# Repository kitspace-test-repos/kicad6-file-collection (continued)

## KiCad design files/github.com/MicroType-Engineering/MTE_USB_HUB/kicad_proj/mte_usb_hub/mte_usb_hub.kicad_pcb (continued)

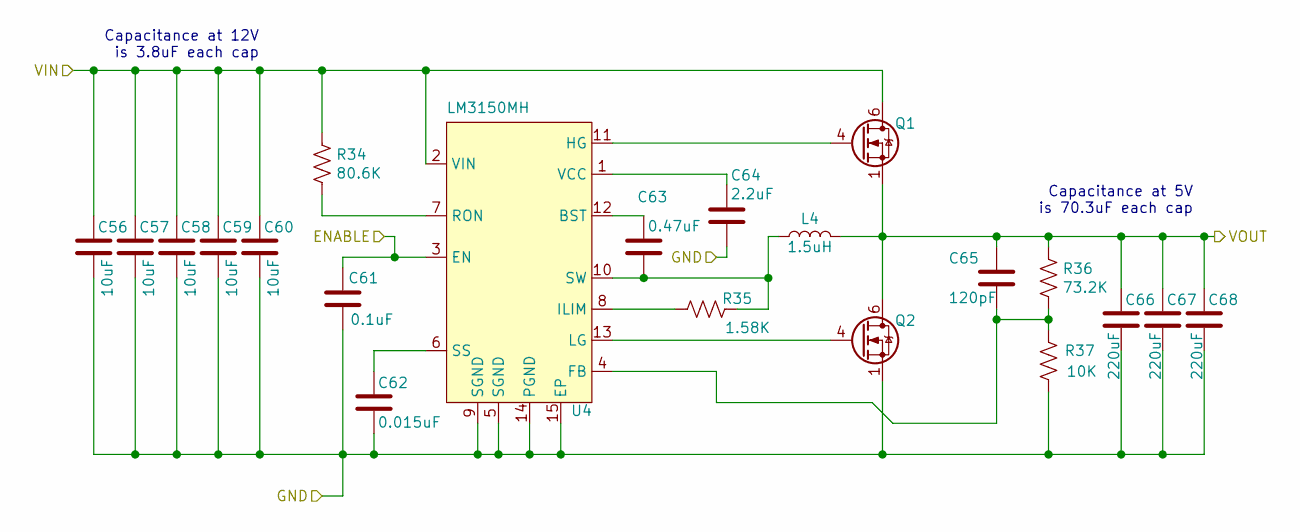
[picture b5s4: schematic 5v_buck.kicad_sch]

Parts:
C56, C57, C58, C59, C60: GRM31CR71E106KA12L; CAPACITOR_1206N
C61: CC0402KRX5R7BB104; CAPACITOR_0402N
C62: TMK105BJ153KV-F; CAPACITOR_0402N
C63: TMK105ABJ474KV-F; CAPACITOR_0402N
C64: TMK105CBJ225MV-F; CAPACITOR_0402N
C65: C0402C121J3GAC7867; CAPACITOR_0402N
C66, C67, C68: GRM32ER60J227ME05L; CAPACITOR_1210N
L4: SRP1270-1R5M; INDM1350X1350X700L250X300N
Q1: CSD16342Q5A
Q2: CSD17577Q5AT; CSD16342Q5A
R34: RC0402FR-0780K6L; RESISTOR_0402N
R35: RC0402FR-071K58L; RESISTOR_0402N
R36: RC0402FR-0773K2L; RESISTOR_0402N
R37: RC0402JR-0710KL; RESISTOR_0402N
U4: LM3150MH; SOP15P65_500X640X110L60X24T310X300N

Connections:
+5V: C65.1, C66.1, C67.1, C68.1, L4.2, Q1.1 (S), Q1.2 (S), Q1.3 (S), Q2.5 (D), Q2.6 (D), Q2.7 (D), Q2.8 (D), R36.1; also elsewhere on the board
+12V: C56.1, C57.1, C58.1, C59.1, C60.1, Q1.5 (D), Q1.6 (D), Q1.7 (D), Q1.8 (D), R34.1, U4.2 (VIN); also elsewhere on the board
/5V Buck/ENABLE: C61.2, U4.3 (EN)
GND: C56.2, C57.2, C58.2, C59.2, C60.2, C61.1, C62.2, C64.2, C66.2, C67.2, C68.2, Q2.1 (S), Q2.2 (S), Q2.3 (S), R37.2, U4.5 (SGND), U4.9 (SGND), U4.14 (PGND), U4.15 (EP); also elsewhere on the board
unnamed: C62.1, U4.6 (SS)
unnamed: C63.1, U4.12 (BST)
unnamed: C63.2, L4.1, R35.2, U4.10 (SW)
unnamed: C64.1, U4.1 (VCC)
unnamed: C65.2, R36.2, R37.1, U4.4 (FB)
unnamed: Q1.4 (G), U4.11 (HG)
unnamed: Q2.4 (G), U4.13 (LG)
unnamed: R34.2, U4.7 (RON)
unnamed: R35.1, U4.8 (ILIM)

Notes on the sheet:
Capacitance at 12V is 3.8uF each cap
Capacitance at 5V is 70.3uF each cap

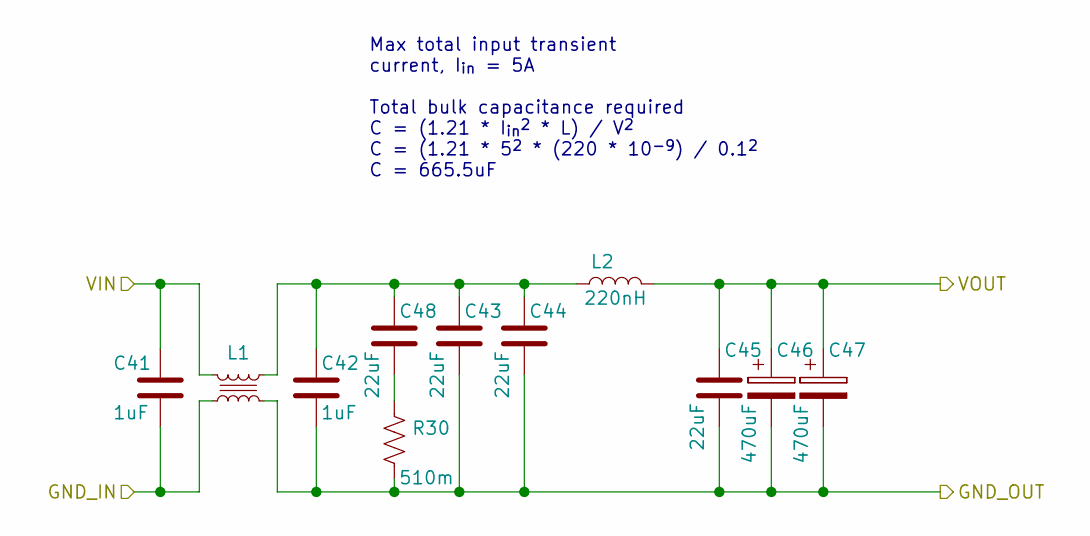
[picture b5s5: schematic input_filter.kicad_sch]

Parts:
C41, C42: CC0603KRX5R9BB105; CAPACITOR_0603N
C43, C44, C45, C48: GCJ32EC71E226KE02; CAPACITOR_1210N
C46, C47: EEE-HAE471UAP; CAPAE1030X1080L350X120N
L1: ACM1211-701-2PL-TL01
L2: FCUL0624-H-R22M=P3; INDM730X660X240L150X140N
R30: RL1206JR-070R51L; RESISTOR_1206N

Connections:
+12V: C45.1, C46.1, C47.1, L2.2; also elsewhere on the board
/INPUT FILTER/GND_IN: C41.2, L1.2; also elsewhere on the board
/INPUT FILTER/VIN: C41.1, L1.1; also elsewhere on the board
GND: C42.2, C43.2, C44.2, C45.2, C46.2, C47.2, L1.3, R30.2; also elsewhere on the board
unnamed: C42.1, C43.1, C44.1, C48.1, L1.4, L2.1
unnamed: C48.2, R30.1

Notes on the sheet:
Max total input transient current, I_{in} = 5A Total bulk capacitance required C = (1.21 * I_{in}^{2} * L) / V^{2} C = (1.21 * 5^{2} * (220 * 10^{-9}) / 0.1^{2} C = 665.5uF

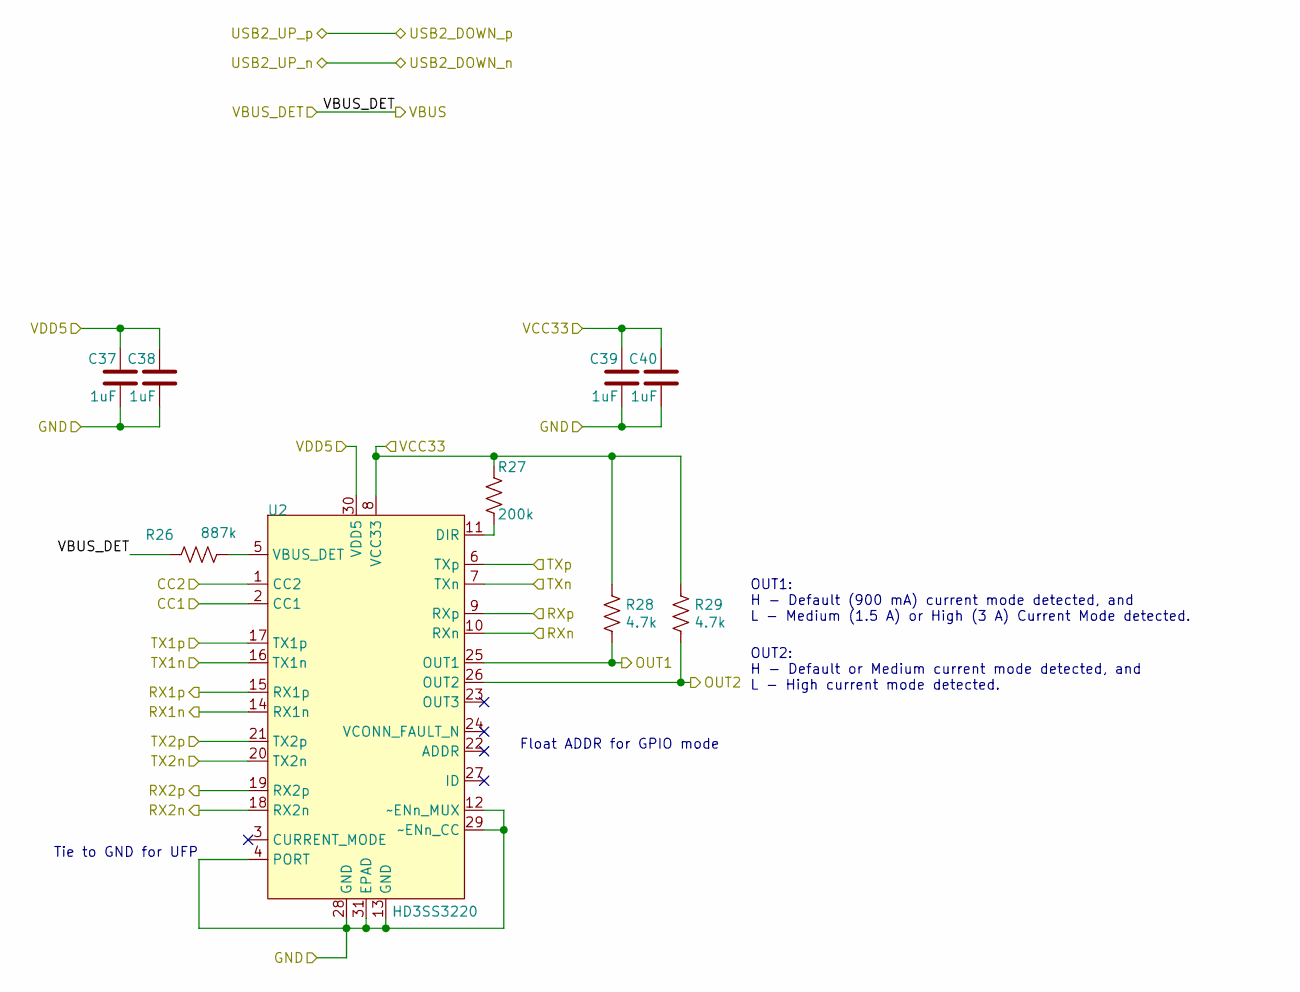
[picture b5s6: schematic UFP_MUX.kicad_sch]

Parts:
C37, C38, C39, C40: CC0402KRX5R7BB105; CAPACITOR_0402N
R26: RC0402FR-07887KL; RESISTOR_0402N
R27: RC0402JR-07200KL; RESISTOR_0402N
R28, R29: RC0402JR-074K7L; RESISTOR_0402N
U2: HD3SS3220; QFN31P40_250X450X80L30X20T120X320N

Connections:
+3V3: C39.1, C40.1, R27.1, R28.1, R29.1, U2.8 (VCC33); also elsewhere on the board
+5V: C37.1, C38.1, U2.30 (VDD5); also elsewhere on the board
/5V_UFP: R26.1; also elsewhere on the board
/RX1_N: U2.14 (RX1n); also elsewhere on the board
/RX1_P: U2.15 (RX1p); also elsewhere on the board
/RX2_N: U2.18 (RX2n); also elsewhere on the board
/RX2_P: U2.19 (RX2p); also elsewhere on the board
/RXN: U2.10 (RXn); also elsewhere on the board
/RXP: U2.9 (RXp); also elsewhere on the board
/TX1_N: U2.16 (TX1n); also elsewhere on the board
/TX1_P: U2.17 (TX1p); also elsewhere on the board
/TX2_N: U2.20 (TX2n); also elsewhere on the board
/TX2_P: U2.21 (TX2p); also elsewhere on the board
/TXN: U2.7 (TXn); also elsewhere on the board
/TXP: U2.6 (TXp); also elsewhere on the board
/UFP_MUX/CC1: U2.2 (CC1); also elsewhere on the board
/UFP_MUX/CC2: U2.1 (CC2); also elsewhere on the board
/UFP_MUX/OUT1: R28.2, U2.25 (OUT1)
/UFP_MUX/OUT2: R29.2, U2.26 (OUT2)
GND: C37.2, C38.2, C39.2, C40.2, U2.4 (PORT), U2.12 (~ENn_MUX), U2.13 (GND), U2.28 (GND), U2.29 (~ENn_CC), U2.31 (EPAD); also elsewhere on the board
unnamed: R26.2, U2.5 (VBUS_DET)
unnamed: R27.2, U2.11 (DIR)

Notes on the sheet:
Tie to GND for UFP
Float ADDR for GPIO mode
OUT1: H - Default (900 mA) current mode detected, and L - Medium (1.5 A) or High (3 A) Current Mode detected.
OUT2: H - Default or Medium current mode detected, and L - High current mode detected.

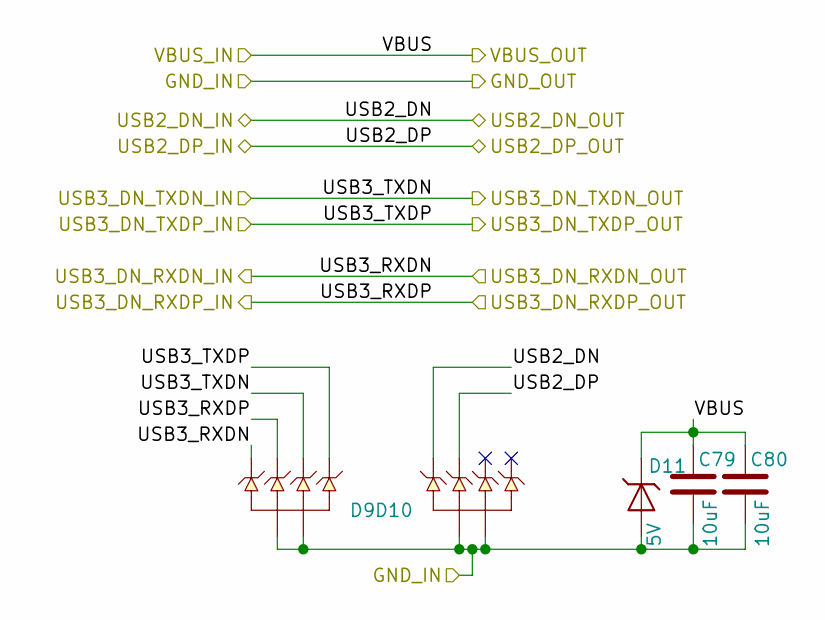
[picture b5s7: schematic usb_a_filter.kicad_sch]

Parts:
C79, C80: GRM21BR61H106ME43; CAPACITOR_0805N
D9, D10: ESD8004MUTAG
D11: ESD9X3.3ST5G; SODFL1006X43N

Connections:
/USB2DN_2_DN: D10.5, D10.6; also elsewhere on the board
/USB2DN_2_DP: D10.4, D10.7; also elsewhere on the board
/USB3DN_2_RXDN: D9.1, D9.10; also elsewhere on the board
/USB3DN_2_RXDP: D9.2, D9.9; also elsewhere on the board
/USB3DN_2_TXDN: D9.4, D9.7; also elsewhere on the board
/USB3DN_2_TXDP: D9.5, D9.6; also elsewhere on the board
/VBUS_2: C79.1, C80.1, D11.C; also elsewhere on the board
GND: C79.2, C80.2, D9.3, D9.8, D10.3, D10.8, D11.A; also elsewhere on the board

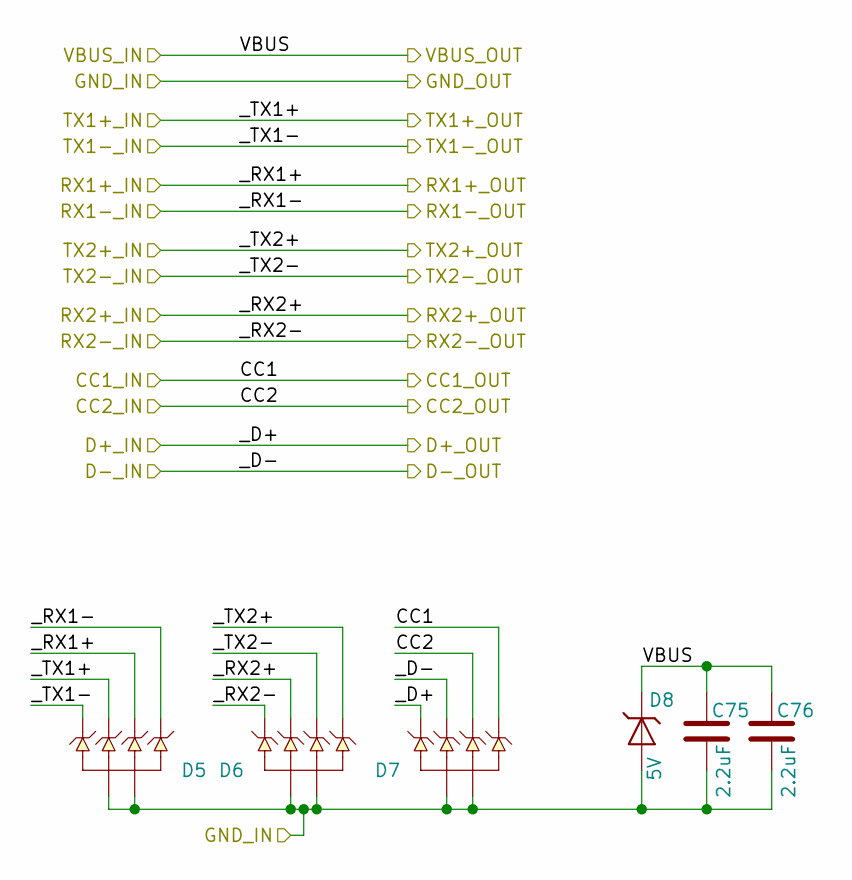
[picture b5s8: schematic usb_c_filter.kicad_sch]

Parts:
C75, C76: TMK105CBJ225MV-F; CAPACITOR_0402N
D5, D6, D7: ESD8004MUTAG
D8: ESD9X3.3ST5G; SODFL1006X43N

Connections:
/5V_UFP: C75.1, C76.1, D8.C; also elsewhere on the board
/RX1_N: D5.5, D5.6; also elsewhere on the board
/RX1_P: D5.4, D5.7; also elsewhere on the board
/RX2_N: D6.5, D6.6; also elsewhere on the board
/RX2_P: D6.4, D6.7; also elsewhere on the board
/UFP_MUX/CC1: D7.1, D7.10; also elsewhere on the board
/UFP_MUX/CC2: D7.2, D7.9; also elsewhere on the board
/USB2_DOWN_N: D7.4, D7.7; also elsewhere on the board
/USB2_DOWN_P: D7.5, D7.6; also elsewhere on the board
/USB_C Filter/_TX1+: D5.2, D5.9; also elsewhere on the board
/USB_C Filter/_TX1-: D5.1, D5.10; also elsewhere on the board
/USB_C Filter/_TX2+: D6.1, D6.10; also elsewhere on the board
/USB_C Filter/_TX2-: D6.2, D6.9; also elsewhere on the board
GND: C75.2, C76.2, D5.3, D5.8, D6.3, D6.8, D7.3, D7.8, D8.A; also elsewhere on the board

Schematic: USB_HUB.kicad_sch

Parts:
C15, C16, C17, C18, C19, C22, C25, C26, C27, C28, C29, C30, C31, C32, C33, C34, C35, C36: CC0402KRX5R7BB105; CAPACITOR_0402N
C20, C23: CC0402JRNPO9BN330; CAPACITOR_0402N
C21, C24: CC0402JRNPO9BN270; CAPACITOR_0402N
R1, R11, R20, R21, R22, R24, R25: RC0402JR-0710KL; RESISTOR_0402N
R2, R3, R4, R5, R6, R7, R8, R9, R10, R16, R17, R18, R19: RC0402JR-0747KL; RESISTOR_0402N
R12, R13, R14: RC0402JR-07200KL; RESISTOR_0402N
R15: RC0402JR-0710RL; RESISTOR_0402N
R23: RT0402DRE0712KL; RESISTOR_0402N
U1: USB7206; QFN101P40_1200X1200X90L60X20T800N
Y1: RH100-25.000-20-F-1030-TR; RH100-12.000-10-2020-EXT-TR

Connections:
+3V3: C28.1, C29.1, C30.1, C31.1, C32.1, C33.1, C34.1, C35.1, R1.2, R20.2, R21.2, R22.2, U1.26 (VDD33), U1.41 (~PRT_DIS_6_M), U1.42 (~PRT_DIS_6_P), U1.43 (VDD33), U1.53 (VDD33), U1.62 (VDD33), U1.67 (VDD33), U1.79 (VDD33), U1.81 (~PRT_DIS_5_P), U1.82 (~PRT_DIS_5_M), U1.88 (VDD33), U1.99 (VDD33); also elsewhere on the board
/1.15V: C15.1, C16.1, C17.1, C18.1, C19.1, C22.1, C25.1, C26.1, C27.1, U1.9 (VCORE), U1.18 (VCORE), U1.25 (VCORE), U1.31 (VCORE), U1.38 (VCORE), U1.55 (VCORE), U1.78 (VCORE), U1.85 (VCORE), U1.93 (VCORE); also elsewhere on the board
/5V_UFP: U1.2 (VBUS_MON_UP); also elsewhere on the board
/PRT_CTL1: U1.60 (PRT_CTL1/OCS)
/PRT_CTL2: U1.59 (PRT_CTL2/OCS)
/PRT_CTL3: U1.58 (PRT_CTL3/OCS)
/PRT_CTL4: U1.57 (PRT_CTL4/OCS)
/RXN: U1.95 (USB3UP_RXDM); also elsewhere on the board
/RXP: U1.94 (USB3UP_RXDP); also elsewhere on the board
/USB2DN_1_DN: U1.6 (USB2DN_1_DM); also elsewhere on the board
/USB2DN_1_DP: U1.5 (USB2DN_1_DP); also elsewhere on the board
/USB2DN_2_DN: U1.15 (USB2DN_2_DM); also elsewhere on the board
/USB2DN_2_DP: U1.14 (USB2DN_2_DP); also elsewhere on the board
/USB2DN_3_DN: U1.28 (USB2DN_3_DM); also elsewhere on the board
/USB2DN_3_DP: U1.27 (USB2DN_3_DP); also elsewhere on the board
/USB2DN_4_DN: U1.35 (USB2DN_4_DM); also elsewhere on the board
/USB2DN_4_DP: U1.34 (USB2DN_4_DP); also elsewhere on the board
/USB2_DOWN_N: U1.90 (USB2UP_DM); also elsewhere on the board
/USB2_DOWN_P: U1.89 (USB2UP_DP); also elsewhere on the board
/USB3DN_1_RXDN: U1.11 (USB3DN_1_RXDM); also elsewhere on the board
/USB3DN_1_RXDP: U1.10 (USB3DN_1_RXDP); also elsewhere on the board
/USB3DN_2_RXDN: U1.17 (USB3DN_2_TXDM); also elsewhere on the board
/USB3DN_2_RXDP: U1.16 (USB3DN_2_TXDP); also elsewhere on the board
/USB3DN_3_RXDN: U1.30 (USB3DN_3_TXDM); also elsewhere on the board
/USB3DN_3_RXDP: U1.29 (USB3DN_3_TXDP); also elsewhere on the board
/USB3DN_4_RXDN: U1.37 (USB3DN_4_TXDM); also elsewhere on the board
/USB3DN_4_RXDP: U1.36 (USB3DN_4_TXDP); also elsewhere on the board
/USB_HUB/USB3DN_1_TXDN: U1.8 (USB3DN_1_TXDM); also elsewhere on the board
/USB_HUB/USB3DN_1_TXDP: U1.7 (USB3DN_1_TXDP); also elsewhere on the board
/USB_HUB/USB3DN_2_TXDN: U1.20 (USB3DN_2_RXDM); also elsewhere on the board
/USB_HUB/USB3DN_2_TXDP: U1.19 (USB3DN_2_RXDP); also elsewhere on the board
/USB_HUB/USB3DN_3_TXDN: U1.33 (USB3DN_3_RXDM); also elsewhere on the board
/USB_HUB/USB3DN_3_TXDP: U1.32 (USB3DN_3_RXDP); also elsewhere on the board
/USB_HUB/USB3DN_4_TXDN: U1.40 (USB3DN_4_RXDM); also elsewhere on the board
/USB_HUB/USB3DN_4_TXDP: U1.39 (USB3DN_4_RXDP); also elsewhere on the board
/USB_HUB/USB3UP_TXDN: U1.92 (USB3UP_TXDM); also elsewhere on the board
/USB_HUB/USB3UP_TXDP: U1.91 (USB3UP_TXDP); also elsewhere on the board
GND: C15.2, C16.2, C17.2, C18.2, C19.2, C20.2, C22.2, C23.2, C25.2, C26.2, C27.2, C28.2, C29.2, C30.2, C31.2, C32.2, C33.2, C34.2, C35.2, C36.2, R2.1, R3.1, R4.1, R5.1, R6.1, R7.1, R8.1, R9.1, R10.1, R11.2, R12.2, R13.2, R14.2, R15.1, R16.1, R17.1, R18.1, R19.1, R23.2, R24.2, R25.2, U1.24 (TESTEN), U1.101 (VSS), Y1.1, Y1.3; also elsewhere on the board
unnamed: C20.1, U1.97 (XTALO), Y1.4
unnamed: C36.1, R1.1, U1.1 (RESET_N)
unnamed: R2.2, U1.44 (I2S_SDI)
unnamed: R3.2, U1.45 (I2S_SDO)
unnamed: R4.2, U1.46 (I2S_CLK)
unnamed: R5.2, U1.47 (I2S_LRCK)
unnamed: R6.2, U1.48 (I2S_MCLK)
unnamed: R7.2, U1.61 (MSTR_I2C_CLK)
unnamed: R8.2, U1.3 (MSTR_I2C_DATA)
unnamed: R9.2, U1.75 (SLV_I2C_CLK)
unnamed: R10.2, U1.76 (SLV_I2C_DAT)
unnamed: R11.1, U1.21 (~CFG_STRAP_1)
unnamed: R12.1, U1.22 (~CFG_STRAP_2)
unnamed: R13.1, U1.23 (~CFG_STRAP_3)
unnamed: R14.1, U1.69 (~CFG_NON_REM)
unnamed: R15.2, U1.70 (~CFG_BC_EN)
unnamed: R16.2, U1.68 (SPI_CLK)
unnamed: R17.2, U1.71 (SPI_D1)
unnamed: R18.2, U1.72 (SPI_D2)
unnamed: R19.2, U1.73 (SPI_D3)
unnamed: R20.1, U1.63 (TEST_1)
unnamed: R21.1, U1.64 (TEST_2)
unnamed: R22.1, U1.65 (TEST_3)
unnamed: R23.1, U1.100 (RBIAS)
unnamed: R24.1, U1.86 (USB3DN_5_RXDP)
unnamed: R25.1, U1.87 (USB3DN_5_RXDM)
unnamed: C23.1, U1.98 (XTALI/CLK_IN), Y1.2

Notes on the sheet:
27pF assume Cstray = 6.5pF 33pF assume Cstray = 3.5pF
CL = (c^{2} / 2c) + C_{stray}
DCP and CDP battery charging on ports 1-4
I2S disabled
I2C disabled
SPI disabled
Only valid config for ~{CFG_STRAP_X and test pins as per datasheet}
All ports removable
Place near IC, connect to GND plane
By default, all ports are configured to non-split mode. PRT_CTLX_U3 floar when not using PortSplit
Unused USB2DN tie to 3v3
Unused USB3DN_TX Float
Unused USB3DN_RX Weak pulldown

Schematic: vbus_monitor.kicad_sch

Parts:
C77, C78: GRM21BR61H106ME43; CAPACITOR_0805N
U6: UCS2114

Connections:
+5V: C77.1, C78.1, U6.3 (COMM_ILIM), U6.6 (V_S), U6.7 (V_S), U6.8 (VDD), U6.9 (VS), U6.10 (VS); also elsewhere on the board
/VBUS_1: U6.4 (VBUS_1), U6.5 (VBUS_1); also elsewhere on the board
/VBUS_4: U6.11 (VBUS_2), U6.12 (VBUS_2); also elsewhere on the board
GND: C77.2, C78.2, U6.1 (PWR_EN_1), U6.2 (GND), U6.13 (BOOST#), U6.14 (GND), U6.15 (PWR_EN_2), U6.16 (~ALERT_2), U6.17 (GND), U6.18 (SMDATA), U6.19 (SMCLK), U6.20 (~ALERT_1); also elsewhere on the board

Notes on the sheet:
EN Active-Low
ILIM = 3.2A

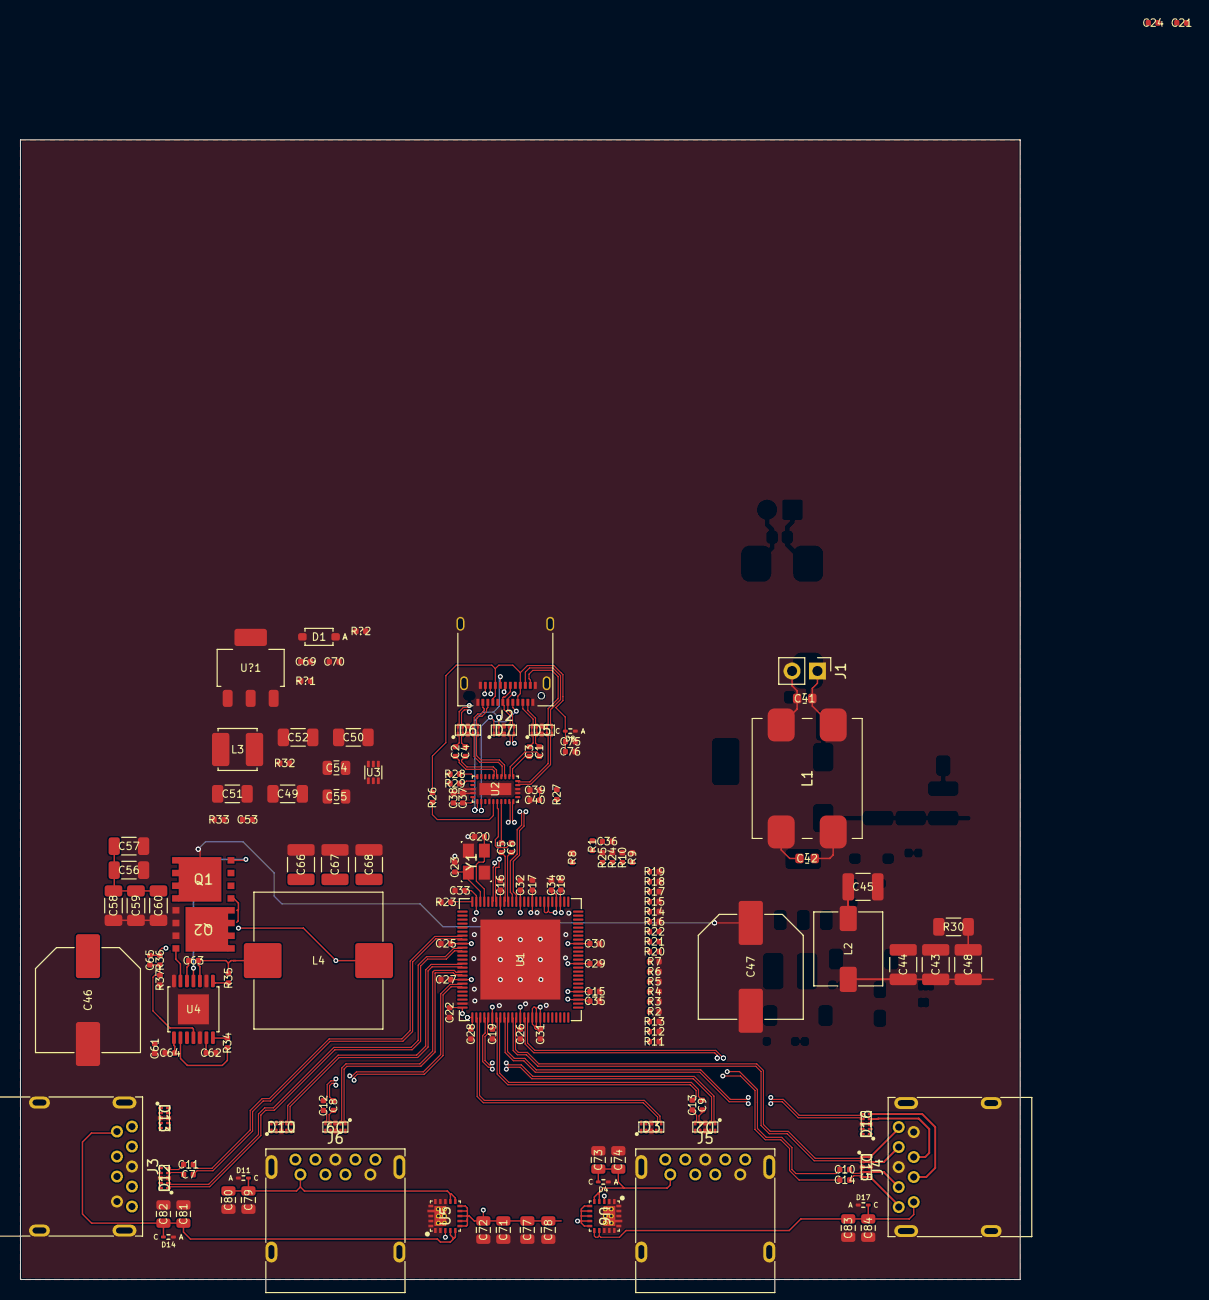
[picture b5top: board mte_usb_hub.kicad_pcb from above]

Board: 6 copper layers, 100.0 x 114.0 mm, 159 parts (0 on the bottom side), 113 nets.

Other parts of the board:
C71, C72, C73, C74, C81, C82, C83, C84: GRM21BR61H106ME43; CAPACITOR_0805N
D2, D3, D12, D13, D15, D16: ESD8004MUTAG
D4, D14, D17: ESD9X3.3ST5G; SODFL1006X43N
U5: UCS2114

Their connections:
+5V: C71.1, C72.1, U5.3 (COMM_ILIM), U5.6 (V_S), U5.7 (V_S), U5.8 (VDD), U5.9 (VS), U5.10 (VS); also elsewhere on the board
/USB2DN_1_DN: D13.5, D13.6; also elsewhere on the board
/USB2DN_1_DP: D13.4, D13.7; also elsewhere on the board
/USB2DN_3_DN: D3.5, D3.6; also elsewhere on the board
/USB2DN_3_DP: D3.4, D3.7; also elsewhere on the board
/USB2DN_4_DN: D16.5, D16.6; also elsewhere on the board
/USB2DN_4_DP: D16.4, D16.7; also elsewhere on the board
/USB3DN_1_RXDN: D12.1, D12.10; also elsewhere on the board
/USB3DN_1_RXDP: D12.2, D12.9; also elsewhere on the board
/USB3DN_1_TXDN: D12.4, D12.7; also elsewhere on the board
/USB3DN_1_TXDP: D12.5, D12.6; also elsewhere on the board
/USB3DN_3_RXDN: D2.1, D2.10; also elsewhere on the board
/USB3DN_3_RXDP: D2.2, D2.9; also elsewhere on the board
/USB3DN_3_TXDN: D2.4, D2.7; also elsewhere on the board
/USB3DN_3_TXDP: D2.5, D2.6; also elsewhere on the board
/USB3DN_4_RXDN: D15.1, D15.10; also elsewhere on the board
/USB3DN_4_RXDP: D15.2, D15.9; also elsewhere on the board
/USB3DN_4_TXDN: D15.4, D15.7; also elsewhere on the board
/USB3DN_4_TXDP: D15.5, D15.6; also elsewhere on the board
/VBUS_1: C73.1, C74.1, D4.C; also elsewhere on the board
/VBUS_2: U5.11 (VBUS_2), U5.12 (VBUS_2); also elsewhere on the board
/VBUS_3: C81.1, C82.1, D14.C, U5.4 (VBUS_1), U5.5 (VBUS_1); also elsewhere on the board
/VBUS_4: C83.1, C84.1, D17.C; also elsewhere on the board
GND: C71.2, C72.2, C73.2, C74.2, C81.2, C82.2, C83.2, C84.2, D2.3, D2.8, D3.3, D3.8, D4.A, D12.3, D12.8, D13.3, D13.8, D14.A, D15.3, D15.8, D16.3, D16.8, D17.A, U5.1 (PWR_EN_1), U5.2 (GND), U5.13 (BOOST#), U5.14 (GND), U5.15 (PWR_EN_2), U5.16 (~ALERT_2), U5.17 (GND), U5.18 (SMDATA), U5.19 (SMCLK), U5.20 (~ALERT_1); also elsewhere on the board

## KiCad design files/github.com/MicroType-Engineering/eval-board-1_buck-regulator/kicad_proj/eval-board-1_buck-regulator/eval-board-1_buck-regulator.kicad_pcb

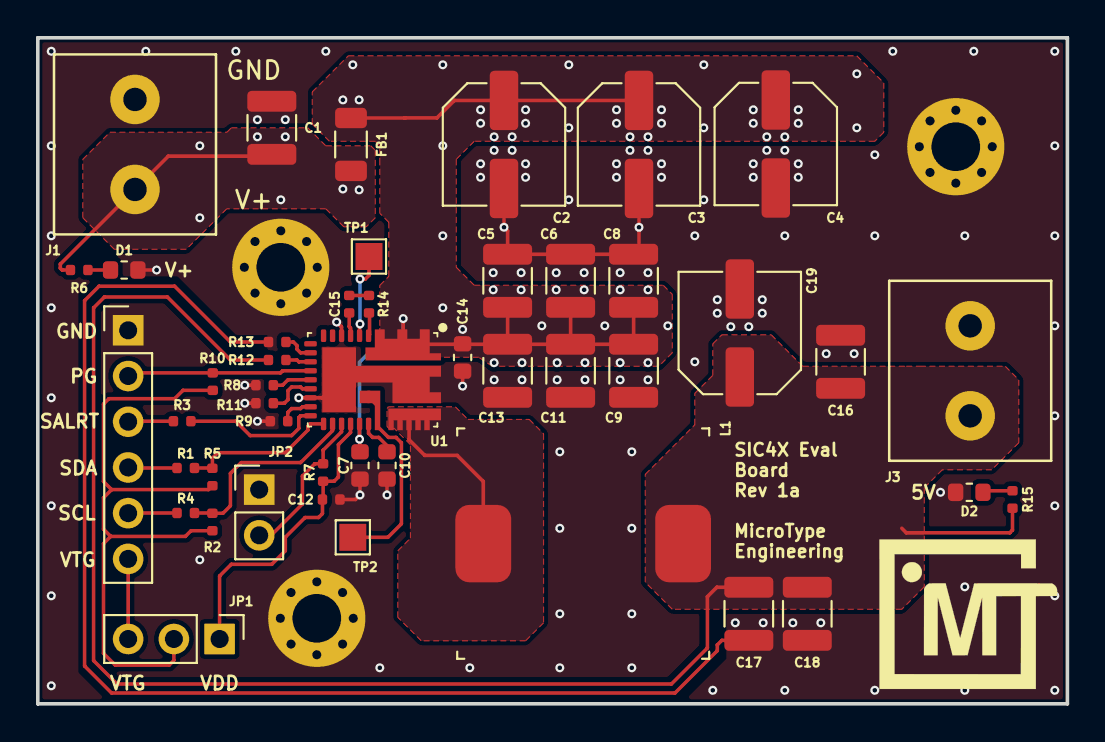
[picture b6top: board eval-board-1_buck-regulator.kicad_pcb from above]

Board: 4 copper layers, 57.2 x 37.0 mm, 49 parts (0 on the bottom side), 29 nets.

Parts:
C1, C16, C17, C18: GRM32ER71C226KEA8; CAPACITOR_1210N
C2, C3, C4, C19: UCH1V470MCS1GS; CAPAE660X580L260X65N
C5, C6, C8, C9, C11, C13: GRM32ER71E226ME15K; CAPACITOR_1210N
C7, C14: GRM188R61H225ME11D; CAPACITOR_0603N
C10: 4.7u; CAPACITOR_0603N
C12: 1u; CAPACITOR_0402N
C15: 0.1uF; CAPACITOR_0402N
D1, D2: LED; CAPACITOR_0603N
FB1: 74279221100; CAPACITOR_1206N
H1, H2, H3: MountingHole_Pad; MountingHole_2.7mm_M2.5_Pad_Via
J1, J3: Conn_01x02; 1935776
J2: Conn_01x06; PinHeader_1x06_P2.54mm_Vertical
JP1: Jumper_NC_Dual; PinHeader_1x03_P2.54mm_Vertical
JP2: Jumper; PinHeader_1x02_P2.54mm_Vertical
L1: PA4343.102NLT; PA4343_PM4343
R1, R3, R4, R15: 220; CAPACITOR_0402N
R2, R5, R7, R10, R12, R13: 10K; CAPACITOR_0402N
R6: 510; CAPACITOR_0402N
R8, R9, R11: 8.87K; CAPACITOR_0402N
R14: 2.2; CAPACITOR_0402N
TP1, TP2: TestPoint; TestPoint_Pad_1.5x1.5mm
U1: SIC453ED-T1-GE3; SiC45X

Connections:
+5V: C16.1, C17.1, C18.1, C19.1, J3.2, L1.2, R12.2, R15.1
+12V: C1.1, FB1.1, J1.2, R6.1
/EN: JP2.2, R7.2, U1.21 (EN)
/EXTERN_VTG: J2.6, JP1.3
/PGOOD: J2.2, R10.2, U1.13 (PGOOD)
/PULLUP_VTG: JP1.2, R2.1, R5.1, R10.1
/SALERT: R3.2, U1.18 (SALRT)
/SCL: R2.2, R4.2, U1.20 (SCL)
/SDA: R1.2, R5.2, U1.19 (SDA)
/VDD: C12.1, JP1.1, R7.1, U1.22 (VDD)
GND: C1.2, C2.2, C3.2, C4.2, C5.2, C6.2, C7.2, C8.2, C9.2, C10.2, C11.2, C12.2, C13.2, C14.2, C16.2, C17.2, C18.2, C19.2, D1.1 (K), D2.1 (K), H1.1, H2.1, H3.1, J1.1, J2.1, J3.1, JP2.1, R8.2, R9.2, R11.2, R13.2, U1.7 (AGND), U1.16 (AGND), U1.32 (PGND)
unnamed: C10.1, U1.24 (PVCC)
unnamed: C2.1, C3.1, C4.1, C5.1, C6.1, C7.1, C8.1, C9.1, C11.1, C13.1, C14.1, FB1.2, U1.1 (PVIN), U1.23 (VIN)
unnamed: C15.1, U1.6 (BOOT)
unnamed: C15.2, R14.1
unnamed: D1.2 (A), R6.2
unnamed: D2.2 (A), R15.2
unnamed: J2.3, R3.1
unnamed: J2.4, R1.1
unnamed: J2.5, R4.1
unnamed: L1.1, U1.26 (SW)
unnamed: R8.1, U1.14 (ADDR)
unnamed: R9.1, U1.17 (RT/SYNC)
unnamed: R11.1, U1.15 (VSET)
unnamed: R12.1, U1.12 (VSEN+)
unnamed: R13.1, U1.11 (VSEN-)
unnamed: R14.2, U1.4 (PH)
unnamed: TP1.1, U1.5 (GH)
unnamed: TP2.1, U1.25 (GL)

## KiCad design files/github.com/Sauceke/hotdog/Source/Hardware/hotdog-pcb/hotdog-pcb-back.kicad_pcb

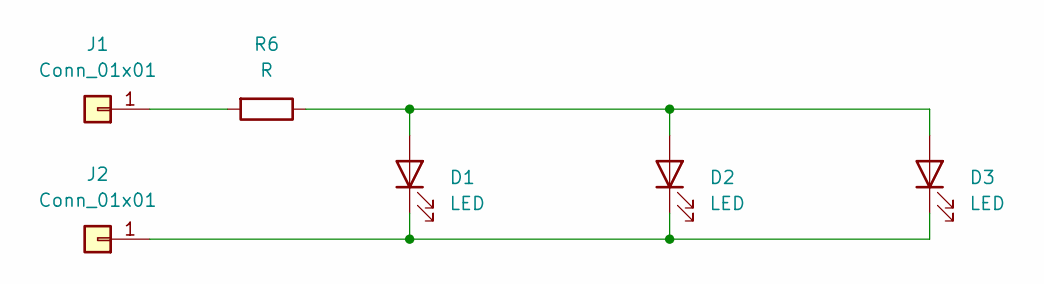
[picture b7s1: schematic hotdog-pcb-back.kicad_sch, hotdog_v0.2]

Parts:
D1, D2, D3: LED; LED_D5.0mm
J1, J2: Conn_01x01; SolderWire-0.1sqmm_1x01_D0.4mm_OD1mm
R6: R; R_Axial_DIN0204_L3.6mm_D1.6mm_P5.08mm_Horizontal

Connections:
unnamed: D1.1 (K), D2.1 (K), D3.1 (K), J2.1
unnamed: D1.2 (A), D2.2 (A), D3.2 (A), R6.1
unnamed: J1.1, R6.2

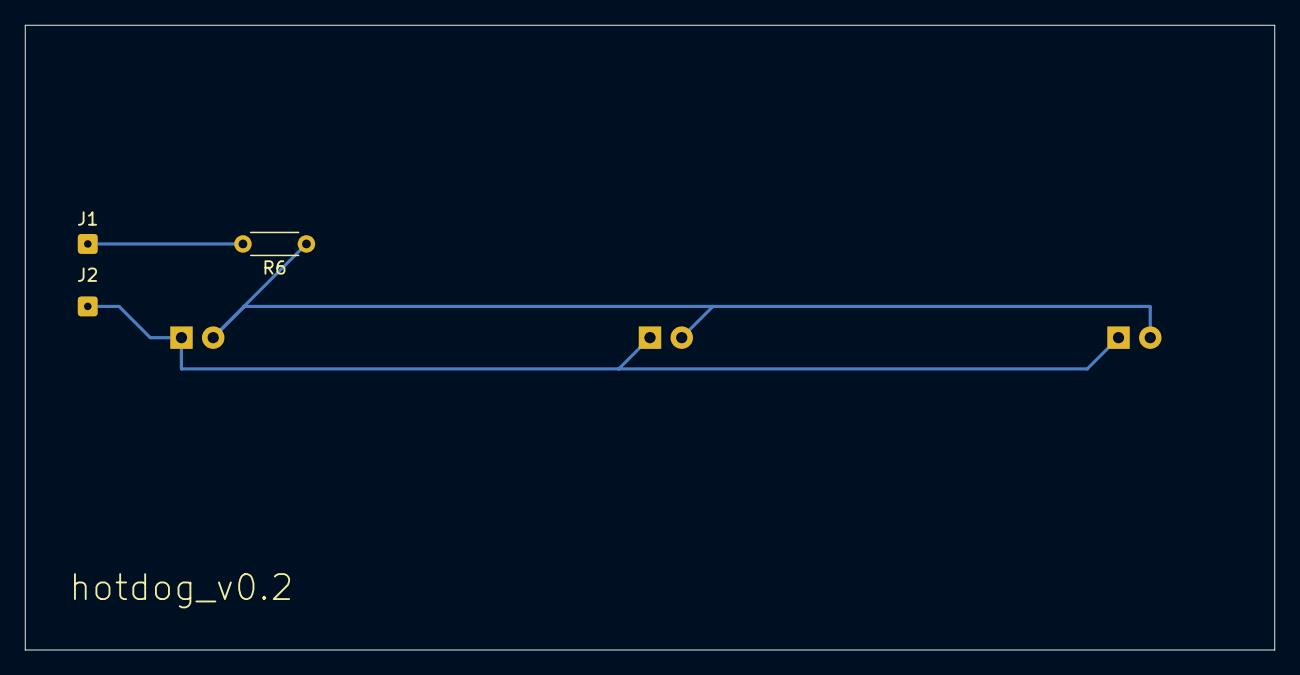
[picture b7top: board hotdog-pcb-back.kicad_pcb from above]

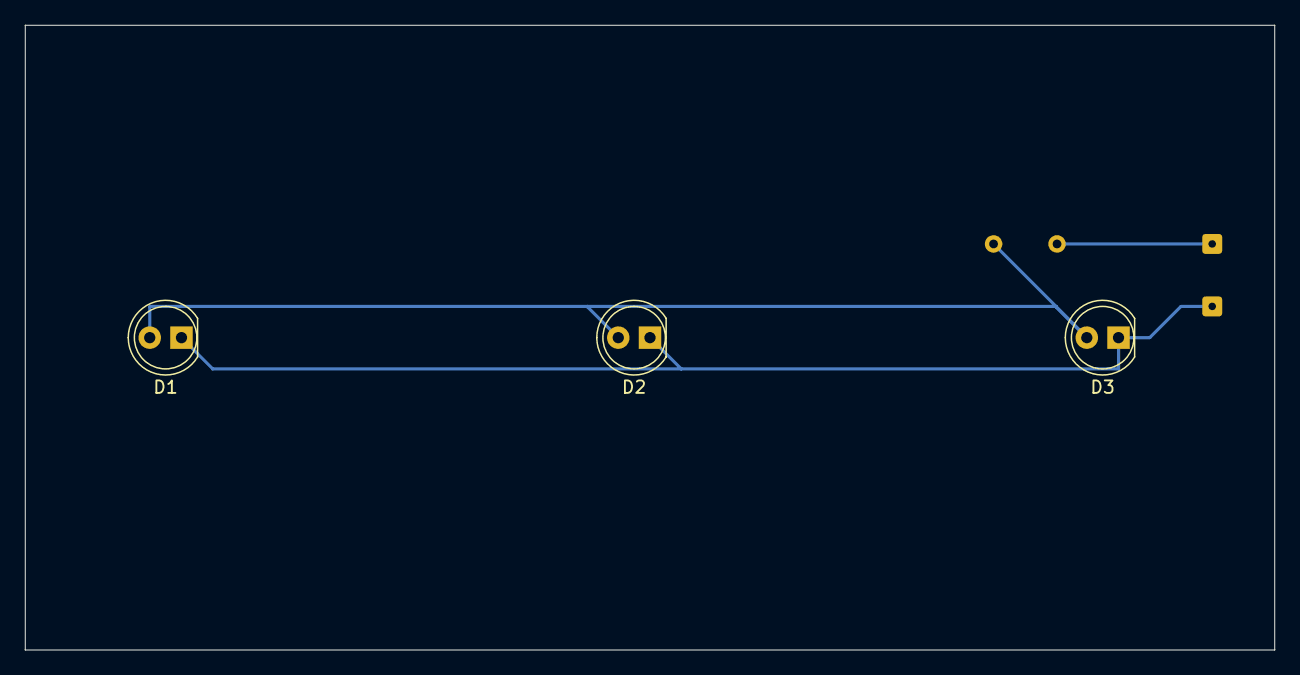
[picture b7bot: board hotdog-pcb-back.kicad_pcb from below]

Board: 2 copper layers, 100.0 x 50.0 mm, 6 parts (3 on the bottom side), 3 nets.
